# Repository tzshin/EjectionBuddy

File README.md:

IMPORTANT: There is a FATAL wiring flaw in the IMU CPOUT capacitor in HW1.0 board!
The other side of that capacitor should connect to ground, NOT 3.3V. Fix it.

You can use some continuity tests
1. Find the falsely connected pad. The pad is shorted to 3.3V.
2. Verify your cutting work. After the cut, the pad should be floating (not shorted to 3.3V or ground).
3. Verify your connecting work. With a decent solder bridge (apply this after hot plate assembly), the pad should be shorted only to ground.

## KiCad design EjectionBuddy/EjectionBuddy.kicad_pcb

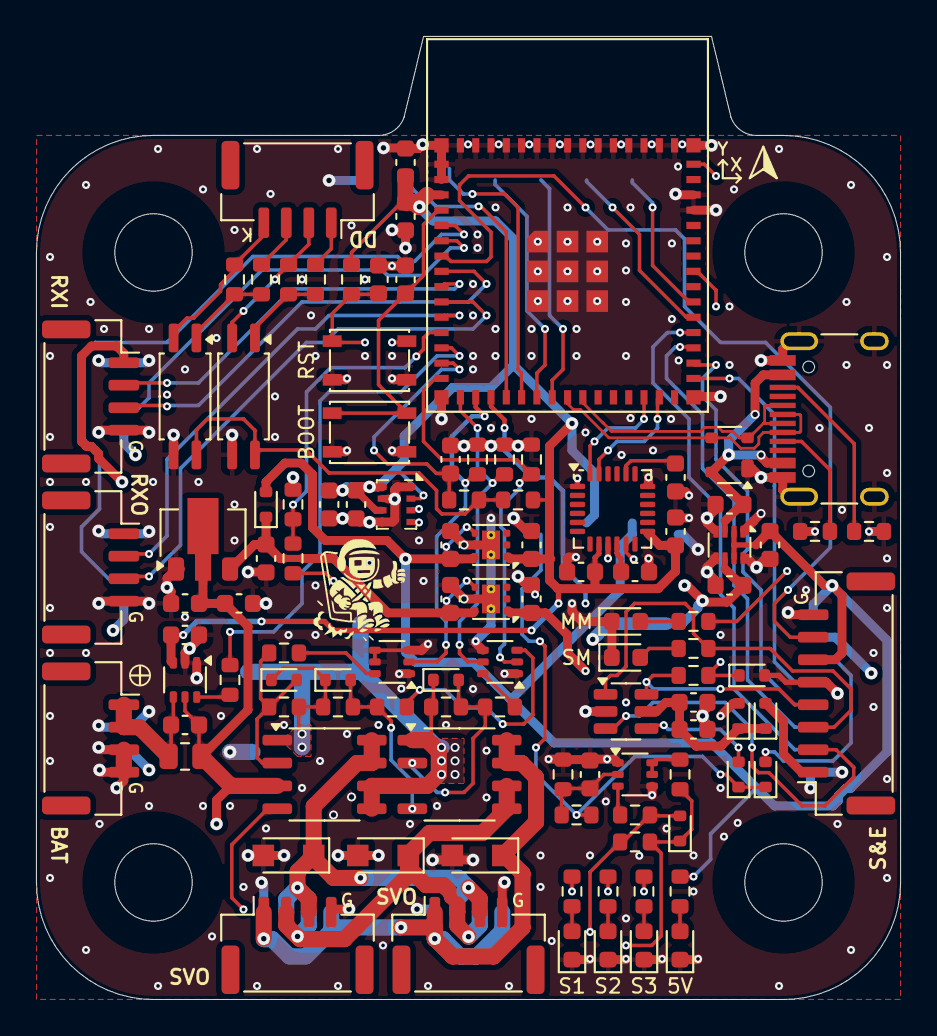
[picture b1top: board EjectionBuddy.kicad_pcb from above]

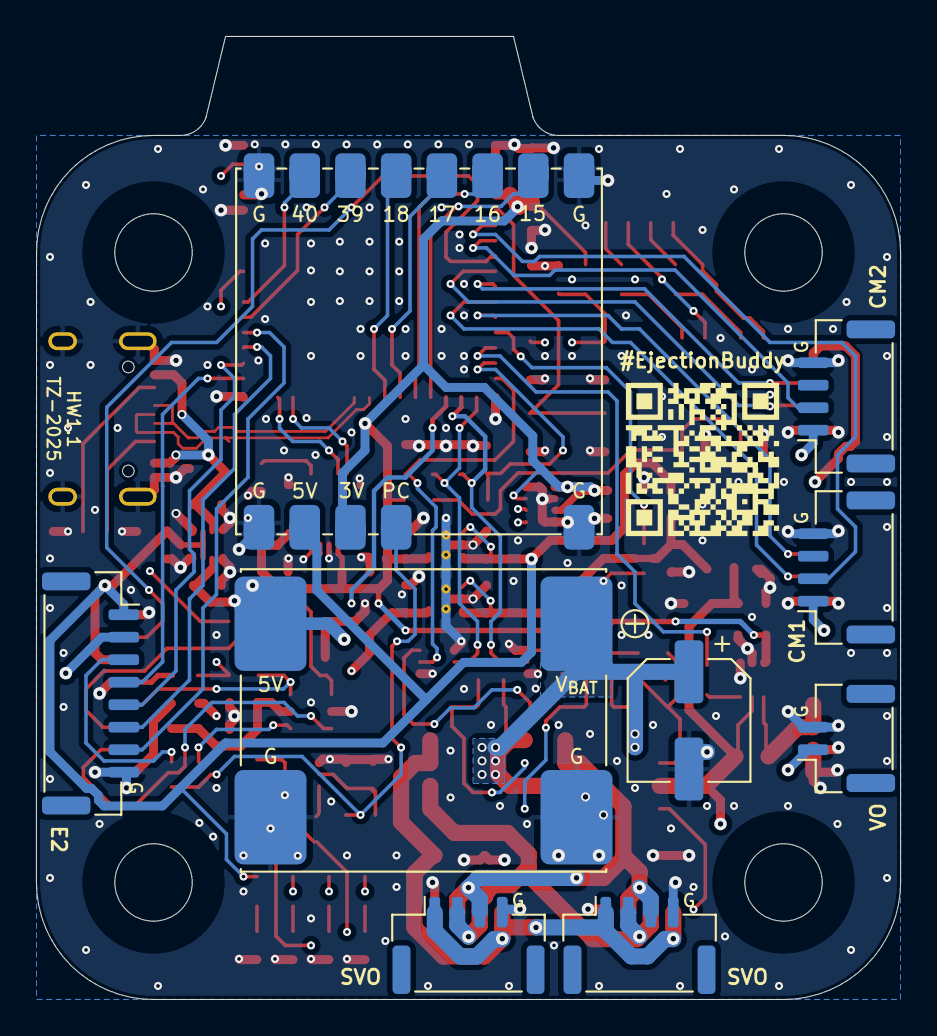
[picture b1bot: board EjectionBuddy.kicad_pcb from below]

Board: 4 copper layers, 48.0 x 53.5 mm, 119 parts (9 on the bottom side), 80 nets.

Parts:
C1, C2, C16, C18, C20, C23, C24, C25, C26: 0.1u; C_0603_1608Metric
C3: 47u; CP_Elec_6.3x5.8
C4, C5, C6, C7, C8, C9, C12, C13, C15, C22: 10u; C_0603_1608Metric
C10, C11, C27: 2.2u; C_0603_1608Metric
C14, C21: 1u; C_0603_1608Metric
C17: 10n; C_0603_1608Metric
C19: 2.2n; C_0603_1608Metric
D1, D9, D11, D12, D13: D_Schottky; D_SOD-523
D2, D3, D4, D8: D_Zener7V5; D_SOD-523
D5, D6, D7: 1N4007; Nexperia_CFP3_SOD-123W
D10: PRTR5V0U2X; SOT-143
D14: D_Zener3V6; D_SOD-523
D15, D16: LED_G; LED_0603_1608Metric
D17, D18, D19, D20: LED_R; LED_0603_1608Metric
H1, H2, H3, H4: MountingHole; HoleNoMask_4.3mm_M4
J1, J2, J3, J4, J5, J6, J7, J8, J10, J11: Conn_01x04; JST_GH_SM04B-GHS-TB_1x04-1MP_P1.25mm_Horizontal
J9: Conn_01x02; JST_GH_SM02B-GHS-TB_1x02-1MP_P1.25mm_Horizontal
J12, J13: Conn_01x08; JST_GH_SM08B-GHS-TB_1x08-1MP_P1.25mm_Horizontal
J14: USB_C_Receptacle_USB2.0_14P; USB_C_Receptacle_HRO_TYPE-C-31-M-12
Q1, Q2: NCE55P04S; SOP-8_3.9x4.9mm_P1.27mm
Q3, Q4, Q5: UMH3N; SOT-363_SC-70-6
R1: 91k; R_0603_1608Metric
R2: 0.05; R_0805_2012Metric
R3, R21, R22, R23: 1k; R_0603_1608Metric
R4, R17, R28, R30, R34: 10k; R_0603_1608Metric
R5, R6, R7, R8, R9, R10, R14, R15, R16: 15k; R_0603_1608Metric
R11, R12, R13, R18, R31, R33: 100k; R_0603_1608Metric
R19, R20: 5.1k; R_0603_1608Metric
R24: 2.7k; R_0603_1608Metric
R25, R26, R27: 39k; R_0603_1608Metric
R29, R32: 400; R_0603_1608Metric
SW1, SW2: SW_Push; SW_SPST_PTS810
U1: INA186A1; SOT-363_SC-70-6
U2: GenericBuck_5V; MP4462BuckModule_TaoBao_20x17
U3: ME6203A50PG; SOT-89-3
U4, U6: LP5912-3.3DRV; WSON-6-1EP_2x2mm_P0.65mm_EP1x1.6mm_ThermalVias
U5: LM66200DRLR; SOT-583-8
U7: ATtiny10-TS; SOT-23-6
U8: MPU-6050; InvenSense_QFN-24_4x4mm_P0.5mm
U9, U10: TLP291; SOIC-4_4.55x2.6mm_P1.27mm
U11: ESP32-S3-MINI-1; ESP32-S2-MINI-1
U12: BMP280; Bosch_LGA-8_2x2.5mm_P0.65mm_ClockwisePinNumbering
U13: EjectionBuddyStamp

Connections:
+3.3S: C8.1, D12.2 (A), U4.1 (OUT)
+3.3V: C1.1, C13.1, C17.1, C18.1, C22.1, C23.1, C26.1, C27.1, R28.2, R34.1, U1.3 (V+), U6.1 (OUT), U8.8 (VLOGIC), U8.13 (VDD), U11.3 (3V3), U12.2 (CSB), U12.6 (VDDIO), U12.8 (VDD), U13.3 (3.3V)
+5C: C9.1, C12.1, D1.2 (A), J12.6, J13.1, R24.1, U5.2 (VOUT), U5.7 (VOUT), U6.4 (EN), U6.6 (IN), U13.2 (5V)
+5S: D11.2 (A), J12.1
+5V: C10.1, J5.1, J10.1, J11.1, U2.3 (5V), U5.6 (VIN2)
/DD_A_1: J7.1, R29.2
/DD_A_2: J7.3, R32.2
/DD_K_1: J7.2, R31.2, U9.2
/DD_K_2: J7.4, R33.2, U10.2
/MM.D+: D10.2 (I/O1), J14.A6 (D+), J14.B6 (D+), U11.24 (IO20)
/MM.D-: D10.3 (I/O2), J14.A7 (D-), J14.B7 (D-), U11.23 (IO19)
/MM.GPIO1: J10.2, U11.5 (IO1)
/MM.GPIO2: J11.2, U11.6 (IO2)
/MM.GPIO3: J12.7, U11.7 (IO3)
/MM.GPIO4: J5.3, U11.8 (IO4)
/MM.GPIO5: J5.2, U11.9 (IO5)
/MM.GPIO6: J6.3, U11.10 (IO6)
/MM.GPIO7: J6.2, U11.11 (IO7)
/MM.GPIO8: R1.2, R4.1, U11.12 (IO8)
/MM.GPIO9: R3.2, U11.13 (IO9)
/MM.GPIO10: C21.1, R30.2, U11.14 (IO10)
/MM.GPIO11: Q3.2 (B1), R11.1, U11.15 (IO11)
/MM.GPIO12: Q3.5 (B2), R12.1, U11.16 (IO12)
/MM.GPIO13: Q4.2 (B1), R13.1, U11.17 (IO13)
/MM.GPIO14: D14.1 (K), R21.2, U11.18 (IO14)
/MM.GPIO15: U11.19 (IO15), U13.5 (IO1)
/MM.GPIO16: U11.20 (IO16), U13.6 (IO2)
/MM.GPIO17: U11.21 (IO17), U13.7 (IO3)
/MM.GPIO18: U11.22 (IO18), U13.8 (IO4)
/MM.GPIO35: J13.4, U11.31 (IO35)
/MM.GPIO36: J13.5, U11.32 (IO36)
/MM.GPIO37: J13.6, U11.33 (IO37)
/MM.GPIO38: J13.7, U11.34 (IO38)
/MM.GPIO39: U11.35 (IO39), U13.9 (IO5)
/MM.GPIO40: U11.36 (IO40), U13.10 (IO6)
/MM.GPIO42: R23.1, U11.38 (IO42)
/MM.SCL: U8.23 (SCL), U11.29 (IO34), U12.4 (SCK)
/MM.SDA: U8.24 (SDA), U11.28 (IO33), U12.3 (SDI)
/SM.RESET: J12.4, R21.1, U7.6 (~RESET/PB3)
/SM.TPICLK: J12.2, U7.3 (PB1)
/SM.TPIDATA: J12.3, R22.1, U7.1 (PB0)
/SW_PWRCUT: D9.1 (K), D13.1 (K), R17.1, U13.4 (SW_PWRCUT)
/main_mcu/0: C25.1, SW2.2, U11.4 (IO0)
/main_mcu/EN: C24.1, R34.2, SW1.2, U11.45 (EN)
/usb/CC1: J14.A5 (CC1), R19.1
/usb/CC2: J14.B5 (CC2), R20.1
GND: C1.2, C3.2, C4.2, C5.2, C6.2, C7.2, C8.2, C9.2, C10.2, C11.2, C12.2, C13.2, C14.2, C15.2, C16.2, C17.2, C18.2, C19.2, C20.2, C21.2, C22.2, C23.2, C24.2, C25.2, C26.2, C27.2, D5.2 (A), D6.2 (A), D7.2 (A), D10.1 (GND), D14.2 (A), D15.1 (K), D16.1 (K), D17.1 (K), D18.1 (K), D19.1 (K), D20.1 (K), J1.4, J2.4, J3.4, J4.4, J5.4, J6.4, J8.3, J8.4, J9.2, J10.4, J11.4, J12.5, J12.8, J13.8, J14.A1 (GND), J14.A12 (GND), J14.B1 (GND), J14.B12 (GND), J14.S1 (SHIELD), Q3.1 (E1), Q3.4 (E2), Q4.1 (E1), Q4.3 (C2), Q4.4 (E2), Q4.5 (B2), Q5.1 (E1), Q5.4 (E2), R4.2, R11.2, R12.2, R13.2, R18.2, R19.2, R20.2, SW1.1, SW2.1, U1.1 (REF), U1.2 (GND), U2.2 (GND), U3.1 (VSS), U4.5 (GND), U4.7 (EP), U5.1 (GND), U5.4 (ON), U5.5 (GND), U5.8 (ST), U6.5 (GND), U6.7 (EP), U7.2 (GND), U8.1 (CLKIN), U8.9 (AD0), U8.11 (FSYNC), U8.18 (GND), U9.3, U10.3, U11.1 (GND), U11.2 (GND), U11.42 (GND), U11.43 (GND), U11.46 (GND), U11.47 (GND), U11.48 (GND), U11.49 (GND), U11.50 (GND), U11.51 (GND), U11.52 (GND), U11.53 (GND), U11.54 (GND), U11.55 (GND), U11.56 (GND), U11.57 (GND), U11.58 (GND), U11.59 (GND), U11.60 (GND), U11.61 (GND), U11.62 (GND), U11.63 (GND), U11.64 (GND), U11.65 (GND), U12.1 (GND), U12.5 (SDO), U12.7 (GND), U13.1 (GND)
unnamed: C6.1, C7.1, D1.1 (K), U3.3 (VOUT), U4.4 (EN), U4.6 (IN)
unnamed: D2.2 (A), Q1.2 (G1), R5.2, R8.1
unnamed: D3.2 (A), Q1.4 (G2), R6.2, R9.1
unnamed: D4.2 (A), Q2.2 (G1), R7.2, R10.1
unnamed: D8.2 (A), Q2.4 (G2), R14.2, R16.1
unnamed: D9.2 (A), J13.3
unnamed: C15.1, C16.1, D11.1 (K), D12.1 (K), U7.5 (VCC)
unnamed: D13.2 (A), U7.4 (PB2)
unnamed: D15.2 (A), R22.2
unnamed: D16.2 (A), R23.2
unnamed: D17.2 (A), R24.2
unnamed: D18.2 (A), R25.2
unnamed: D19.2 (A), R26.2
unnamed: D20.2 (A), R27.2
unnamed: Q3.6 (C1), R8.2
unnamed: Q3.3 (C2), R9.2
unnamed: Q4.6 (C1), R10.2
unnamed: C14.1, Q5.2 (B1), R17.2, R18.1
unnamed: Q5.5 (B2), Q5.6 (C1), R15.2
unnamed: Q5.3 (C2), R16.2
unnamed: R3.1, U1.6
unnamed: R28.1, R30.1, U9.4, U10.4
unnamed: R29.1, R31.1, U9.1
unnamed: R32.1, R33.1, U10.1
unnamed: C19.1, U8.20 (CPOUT)
unnamed: C20.1, U8.10 (REGOUT)
SVO1: D5.1 (K), J1.1, J2.1, J3.1, J4.1, Q1.7 (D1), Q1.8 (D1), R25.1
SVO2: D6.1 (K), J1.2, J2.2, J3.2, J4.2, Q1.5 (D2), Q1.6 (D2), R26.1
SVO3: D7.1 (K), J1.3, J2.3, J3.3, J4.3, Q2.7 (D1), Q2.8 (D1), R27.1
VBAT: C2.1, J8.1, J8.2, R2.1, U1.4 (+)
VM: C3.1, D2.1 (K), D3.1 (K), D4.1 (K), J9.1, Q1.1 (S1), Q1.3 (S2), Q2.1 (S1), Q2.5 (D2), Q2.6 (D2), R1.1, R5.1, R6.1, R7.1, U2.1 (VIN)
VS: C2.2, C4.1, C5.1, D8.1 (K), J13.2, Q2.3 (S2), R2.2, R14.1, R15.1, U1.5 (-), U3.2 (VIN)
VUSB: C11.1, D10.4 (VCC), J14.A4 (VBUS), J14.A9 (VBUS), J14.B4 (VBUS), J14.B9 (VBUS), U5.3 (VIN1)

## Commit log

2025-04-03 Schematic half finished, a second MCU waiting to be implemented
2025-04-04 More work on the side-mcu, ongoing
2025-04-13 Finished! QR and instruction pending
2025-04-13 Slight improvements on routing and schematic
2025-04-18 Side-mcu stm -> attiny, with improvements here and there
2025-04-18 Prodection version hw1.0 finished, with tidy-ups and bug-fixes
2025-04-18 Fix the e-cap footprint, we'll keep the 1.0
2025-04-18 Add Vbat voltage limit warning to schematic
2025-04-18 Untrack sch renaming poop and renamed connecter.sch to connector.sch
2025-04-20 Fixed a FATAL imu wiring fault, CPOUT
2025-07-23 Freeze for launch July 2025
